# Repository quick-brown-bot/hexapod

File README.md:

# Hexapod

An ESP32-powered hexapod robot built as a long-term robotics and embedded systems project.

The goal is not just to make a robot walk, but to learn and at the same time build a platform that is easy to experiment with, tune, and extend. Most robot behavior is configurable at runtime, control inputs are transport-independent, and the motion stack is organized into separated components.

The project combines firmware, hardware design, and system documentation in a single repository.

> 6 legs, 18 servos, ESP32, ESP-IDF, FreeRTOS, direct PWM.

The distributed RS485/RP2040 leg-controller generation of this project has moved to a separate repository: [quick-brown-bot/hexapod_v2](https://github.com/quick-brown-bot/hexapod_v2). This repo covers the original ESP32 direct-PWM robot only. V1 is closed: the hardware and firmware here are done and kept for reference and continued use, not further development.

---

## What Is In This Repository

The repository contains software and hardware assets used to develop and validate the robot.

```text
firmware/
└── mainboard/         Main robot firmware (ESP32, direct PWM)

hardware/
├── servo_mainboard/   Central ESP32 board driving the servos directly
├── leg/               Leg controller board
├── esp32_connector/   ESP32 carrier / breakout
├── symbols/           Symbol libraries
├── footprints/        Footprint libraries
└── models/            Mechanical models

docs/
├── common/            Docs shared across subsystems (RPC, WiFi, config)
├── architecture/       System and hardware architecture docs
├── development/        Development docs
└── plans/             Project-wide backlog and research items
```

Mainboard firmware overview: [firmware/mainboard/README.md](firmware/mainboard/README.md)

The main firmware is built around a fixed 100 Hz control loop and a modular motion pipeline:

```text
Controller Input
        ↓
Gait Scheduler
        ↓
Foot Trajectory Generation
        ↓
Inverse Kinematics
        ↓
Motion Limiting
        ↓
Servo Outputs
```

---

## Current Technical Highlights

## Effort Summary

| Effort Area | Scope | Current Status | Notes |
| --- | --- | --- | --- |
| Locomotion Pipeline | Command mapping, gait scheduler, swing trajectory, whole-body IK | Implemented | Runs in a fixed 100 Hz control loop |
| KPP Motion Limits | Velocity, acceleration, jerk limiting and state estimation | Implemented | Runtime limits are configuration-backed |
| Controller Abstraction | Driver-agnostic core plus transport-specific drivers | Implemented | FlySky iBUS, Wi-Fi TCP, and Bluetooth Classic paths are present |
| RPC System | Queue-based command processing and config control | Implemented | Live inspection and runtime tuning are available |
| Configuration Platform | Namespace defaults, migration, discovery, persistence | Implemented | Core runtime namespaces are already consumed by modules |
| Configurator Tooling | External tuning and visualization UX | Planned | Firmware-side groundwork exists; UI work remains |

## Hardware Snapshot

- MCU: ESP32 running FreeRTOS through ESP-IDF.
- Robot layout: 6 legs, 3 degrees of freedom per leg, 18 hobby servos total.
- Power: 4S LiPo, separate UBEC paths for servo and logic power.
- PWM: mixed MCPWM and LEDC to reach all 18 outputs on the ESP32.
- Mechanical: custom 3D-printed chassis and leg parts.

## High-Level Architecture

```mermaid
flowchart LR
        Control[Controller stack]
        Config[RPC and config]
        App[Application loop]
        Loc[Locomotion]
        Limits[Motion limiting]
        Act[Actuation]
        Robot[Robot hardware]

        Control --> App
        Config --> App
        App --> Loc --> Limits --> Act --> Robot
        Config --> Control
```

- Controller stack: receives operator input from supported transports and normalizes it.
- RPC and config: handles runtime commands, parameter discovery, persistence, and save flows.
- Application loop: owns boot order and the 100 Hz control cycle.
- Locomotion: turns operator intent into gait phase, foot targets, and joint-space commands.
- Motion limiting: constrains commanded motion to configured dynamic envelopes.
- Actuation: maps joint commands to the PWM outputs that drive the robot.

### Runtime Configuration

Configuration is treated as a first-class subsystem rather than a collection of compile-time constants.

Parameters are organized into namespaces. Each namespace owns:

- parameter definitions,
- default values,
- validation rules,
- persistence behavior,
- migration logic,
- RPC discovery metadata.

The configuration manager provides:

- runtime parameter inspection,
- runtime modification,
- save/load operations,
- namespace registration,
- NVS persistence,
- version-aware migration support.

Robot geometry, calibration data, controller settings, motion limits, and other runtime behavior are loaded through this system rather than being hardcoded throughout the codebase.

### Motion Pipeline

The locomotion stack converts user commands into joint targets through a sequence of dedicated subsystems:

- gait scheduling,
- swing trajectory generation,
- inverse kinematics,
- velocity limiting,
- acceleration limiting,
- jerk limiting,
- servo actuation.

The motion loop runs at 100 Hz.

### Controller Abstraction

Controller transports are separated from locomotion.

Supported ingress paths currently include:

- FlySky iBUS,
- Wi-Fi TCP,
- Bluetooth Classic.

Each transport driver translates incoming data into a normalized controller state consumed by the motion system.

This allows locomotion, gait generation, and motion limiting to remain independent of transport-specific protocols.

### Hardware-Aware Design

The robot uses 18 servos arranged as three joints per leg:

- Coxa
- Femur
- Tibia

Servo signal generation is implemented on ESP32 using a combination of MCPWM and LEDC peripherals to fit within available hardware resources.

Power for logic and servos is separated to improve stability under heavy load.

---

## Engineering Problems Being Explored

This project is primarily a learning and engineering platform.

Current focus areas include:

- real-time control on resource-constrained hardware,
- gait generation and scheduling,
- inverse kinematics,
- motion smoothing and trajectory constraints,
- configuration architecture for embedded systems,
- transport-independent control interfaces,
- robotics software maintainability,
- practical servo-driven locomotion.

---

## Documentation

The repository contains detailed documentation covering implementation details and architecture decisions.

- [docs/architecture/SYSTEM_ARCHITECTURE.md](docs/architecture/SYSTEM_ARCHITECTURE.md)
- [docs/architecture/HARDWARE_AND_MECHANICS.md](docs/architecture/HARDWARE_AND_MECHANICS.md)
- [firmware/mainboard/README.md](firmware/mainboard/README.md)

**Common:**
- [docs/common/interfaces/RPC_USER_GUIDE.md](docs/common/interfaces/RPC_USER_GUIDE.md)
- [docs/common/configuration/CONFIGURATION_PERSISTENCE_DESIGN.md](docs/common/configuration/CONFIGURATION_PERSISTENCE_DESIGN.md)

Full documentation index: [docs/README.md](docs/README.md)

---

## Project Status

The project is under active development.

Current work focuses on improving locomotion quality, refining control architecture boundaries, and preparing the next generation of leg electronics while keeping the existing robot operational as a test platform.

---

## License

This repository uses Apache License 2.0 for the mainboard firmware.

License file location: [LICENSE](LICENSE)

Include the following notice in derivative works:

```text
Copyright 2025 Pawel Grudzien

Licensed under the Apache License, Version 2.0 (the "License");
you may not use this file except in compliance with the License.
You may obtain a copy of the License at

    http://www.apache.org/licenses/LICENSE-2.0

Unless required by applicable law or agreed to in writing, software
distributed under the License is distributed on an "AS IS" BASIS,
WITHOUT WARRANTIES OR CONDITIONS OF ANY KIND, either express or implied.
See the License for the specific language governing permissions and
limitations under the License.
```

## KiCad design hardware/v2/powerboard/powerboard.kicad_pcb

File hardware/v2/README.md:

# Hexapod V2 boards

Schematics for the [V2 system architecture](../../docs/architecture/HEXAPOD_V2_SYSTEM_ARCHITECTURE.md):
distributed leg controllers with logic power separated from servo power. V1
(`hardware/servo_mainboard`, `hardware/leg`, `hardware/esp32_connector`) is left
untouched — V2 lives here in parallel.

Three boards:

| Board | Source | Role |
|-------|--------|------|
| [MainBoard](mainboard/) | [`mainboard_sch.py`](mainboard/mainboard_sch.py) | ESP32 + IMU + RS485 master + 6× RJ11. Logic & comms only. |
| [LegBoard](legboard/) | [`legboard_sch.py`](legboard/legboard_sch.py) | XIAO RP2040 + SP3485 + 3 servos + sensing. One per leg. |
| [MainPowerBoard](powerboard/) | [`powerboard_sch.py`](powerboard/powerboard_sch.py) | Battery → fuse/switch/protection → 3 UBECs + SBEC → legs. |

These schematics are authored **as code** with the
[`hardware-schematics`](../schematic/README.md) toolchain. The Python script is
the source of truth; `uuids.json` is the committed UUID registry that protects
the PCB layout across regenerations. Edit the `.py`, never the `.kicad_sch` by
hand.

## Regenerating

```bash
python hardware/v2/mainboard/mainboard_sch.py
python hardware/v2/legboard/legboard_sch.py
python hardware/v2/powerboard/powerboard_sch.py
```

Each writes its `<board>.kicad_sch` and updates `<board>/uuids.json` (additions
only for unchanged parts). `hardware/v2/_common.py` resolves symbol libraries:
stock KiCad libs from the install (override with `KICAD_SYMBOL_DIR`), plus the
v2-local libraries under [`symbols/`](symbols/) — the Seeed XIAO series
(`Seeed_Studio_XIAO_Series.kicad_sym`), the ESP32 module (`SymbolsLib.kicad_sym`),
and `Hexapod_V2.kicad_sym` (flattened standalone `RJ25` and `SP3485CN`, because
the stock library defines those as derived `(extends …)` symbols the code
importer cannot follow).

V2 is self-contained: its own copy of the symbol libraries, footprints, and the
v2 FreeCAD model live here under [`symbols/`](symbols/), [`footprints/`](footprints/)
and [`models/`](models/); the boards do not depend on shared top-level libraries.

## Inter-board connections

```text
MainPowerBoard.J_LOGIC (+5V) ──► MainBoard.J7 (SBEC_5V_IN)
MainBoard.J1..J6 (RJ11)      ──► LegBoard.J1 (UPLINK_RJ11)        ×6
MainPowerBoard.J1..J6 (+6V)  ──► LegBoard.J5 (SERVO_PWR_IN)       ×6
```

### RJ11 / RJ25 leg link (MainBoard ↔ LegBoard)

The physical cable is populated as a 4-wire link inside a 6P6C/RJ25 shell, so
pins 1 and 6 are intentionally left unconnected.

| Pin | Net | Function |
|-----|-----|----------|
| 1 | — | unused |
| 2 | GND | Ground |
| 3 | RS485_A | RS485 A |
| 4 | RS485_B | RS485 B |
| 5 | +5V | Logic power |
| 6 | — | unused |

## MainBoard nets

| Net | Connects |
|-----|----------|
| `+5V` | SBEC input (J7), ESP32 dev-board VIN, all six RJ11 pin 5 |
| `+3.3V` | ESP32 dev-board 3V3 output, SP3485 VCC, IMU, decoupling, EN pull-up |
| `GND` | global ground |
| `ESP_TXD` / `ESP_RXD` | ESP32 IO17/IO16 (UART2) ↔ SP3485 DI/RO |
| `RS485_DE` | ESP32 IO4 → SP3485 DE + ~RE (direction) |
| `RS485_A` / `RS485_B` | SP3485 A/B ↔ all six RJ11, 120 Ω term (R1) |
| `IMU_SDA` / `IMU_SCL` / `IMU_INT` | ESP32 IO21/IO22/IO34 ↔ IMU header (J9) |

MainBoard decoupling intent (implemented in schematic code): `C1` 10 uF on +5V at
power entry (close to J7/U1 VIN), `C2` 100 nF at ESP32 3V3 pins, `C3` 100 nF at
SP3485 VCC, `C4` 100 nF at IMU header power pins, and `C5` 10 uF bulk on +3.3V
near the ESP32 3V3-source/load hub.

IMU header J9 (`Conn_01x05`): 1 = +3.3V, 2 = GND, 3 = SDA, 4 = SCL, 5 = INT.

Footprints currently driven from the generator: `U1` uses
`Custom:ESP32_Dev_Board`, `J1..J6` use
`Connector_RJ:RJ25_Wayconn_MJEA-660X1_Horizontal`, `J9` uses
`Connector_PinHeader_2.54mm:PinHeader_1x05_P2.54mm_Vertical`, `U2` uses the
SOIC-8 SP3485 footprint, and the ordinary small R/C parts default to 0805.

## LegBoard nets

| Net | Connects |
|-----|----------|
| `+5V` | RJ11 pin 5 logic power → XIAO VBUS (U1.14) |
| `+3.3V` | XIAO 3V3 out (U1.12) → SP3485 VCC, INA4181 VCC, decoupling |
| `+6V` | post-total-shunt servo bus; high-side **force** node feeding the three per-servo branch shunts and bulk cap C2 |
| `+6V_IN` | raw servo-power input (J5) ahead of the total shunt |
| `+6V_COXA` / `+6V_FEMUR` / `+6V_TIBIA` | post-branch-shunt servo supply rails (force) for J2 / J3 / J4 |
| `ITOT_SP` / `ITOT_SN` | Kelvin **sense** taps of total shunt R4 → INA IN+1 / IN-1 |
| `COXA_SP` / `COXA_SN` | Kelvin sense taps of coxa shunt R5 → INA IN+4 / IN-4 |
| `FEMUR_SP` / `FEMUR_SN` | Kelvin sense taps of femur shunt R3 → INA IN+2 / IN-2 |
| `TIBIA_SP` / `TIBIA_SN` | Kelvin sense taps of tibia shunt R2 → INA IN+3 / IN-3 |
| `GND` | global ground |
| `RP_TXD` / `RP_RXD` | XIAO P0/P1 (UART) ↔ SP3485 DI/RO |
| `RS485_DE` | XIAO P6/D4 → SP3485 DE + ~RE |
| `RS485_A` / `RS485_B` | SP3485 ↔ RJ11, 120 Ω term R1 (DNP except bus ends) |
| `COXA_PWM` / `FEMUR_PWM` / `TIBIA_PWM` | XIAO P3/P4/P2 → servo connectors J2/J3/J4 |
| `I_TOTAL_SENSE` | INA4181 channel 1 output → XIAO A0 |
| `I_FEMUR_SENSE` | INA4181 channel 2 output → XIAO A1 |
| `I_TIBIA_SENSE` | INA4181 channel 3 output → XIAO A2 |
| `I_COXA_SENSE` | INA4181 channel 4 output → XIAO A3 |

Servo connectors J2/J3/J4 (`Conn_01x03`): 1 = signal, 2 = branch +6V, 3 = GND.
J5 is a 2-pin screw terminal for servo power input. The four current shunts
`R2`/`R3`/`R4`/`R5` are **4-terminal (Kelvin) shunts** (`Device:R_Shunt`): pins
1/4 carry current, pins 2/3 are the sense taps. Each INA input reaches the shunt
over its own unique two-node `*_SP`/`*_SN` net, so the autorouter cannot merge
the three high-side taps (INA pins 6/15/17) through the shared `+6V` copper or
assign them current-rail trace widths. U3 (`INA4181A3IPWR`, gain 100) measures channel 1 across the total-leg shunt
`R4` (`+6V_IN`→`+6V`), channel 2 across femur `R3`, channel 3 across tibia
`R2`, channel 4 across coxa `R5`; IN+ is always on the higher-potential
(source) side. The generated sheet layout keeps the XIAO and INA
blocks as top-level anchors with the connector and power groups below for
readability.

> **Shunt placement must stay at rotation 0.** The schematic-as-code pin
> transform mismatches KiCad for off-axis pins at rotation 90/270 — the Kelvin
> sense pads land off the pin and the force pads swap. Verified via netlist
> export; keep the `Device:R_Shunt` placements un-rotated.

Footprints currently driven from the generator: `U1` uses
`Seeed_Studio_XIAO_Series:XIAO-RP2040-DIP`, `J1` uses
`Connector_RJ:RJ25_Wayconn_MJEA-660X1_Horizontal`, `U2` uses the SOIC-8
SP3485 footprint, `U3` uses `Custom:PW20_TEX`, `J2`/`J3`/`J4` use
`Connector_PinHeader_2.54mm:PinHeader_1x03_P2.54mm_Vertical`, `J5` uses
`TerminalBlock:TerminalBlock_MaiXu_MX126-5.0-02P_1x02_P5.00mm`, the four INA
shunts now use the 4-contact Kelvin footprint
`Resistor_SMD:R_Shunt_Ohmite_LVK12`, `C2` uses the through-hole radial candidate
`Capacitor_THT:CP_Radial_D8.0mm_P3.50mm` for an 8 mm diameter bulk capacitor, and
the ordinary small R/C parts default to 0805. Verify the LVK12 shunt power rating
and the capacitor lead pitch / body height against the exact parts before
freezing the PCB.

## MainPowerBoard nets

| Net | Connects |
|-----|----------|
| `BATT_RAW`→`BATT_FUSED`→`+VMAIN` | battery → F1 fuse → Q1/Q2 parallel PMOS reverse-polarity stage → main rail |
| `+VMAIN` | feeds the three UBEC modules (J8/J9/J10), the SBEC (J11), monitor (J13), bulk C4 |
| `VSERVO1` | UBEC1 out → legs 1,2 (J1,J2), bulk C1, LED D2 |
| `VSERVO2` | UBEC2 out → legs 3,4 (J3,J4), bulk C2, LED D3 |
| `VSERVO3` | UBEC3 out → legs 5,6 (J5,J6), bulk C3, LED D4 |
| `+5V` | SBEC out (J11) → logic output (J12), LED D5 |
| `GND` | global ground |

UBEC/SBEC module headers (`Conn_01x04`): 1 = +VMAIN in, 2 = GND, 3 = regulated
out, 4 = GND. Monitor header J13 (`Conn_01x05`): +VMAIN, VSERVO1, VSERVO2,
VSERVO3, GND.

`F1` is a soldered-in (non-replaceable) SMD fuse, Schurter 3413.0331.22
(20A, time-lag, 1206/`Fuse:Fuse_1206_3216Metric`) — chosen over an automotive
mini-blade holder because TME stocks no SMD blade-fuse holder; the previous
`Custom:Fuse Holder Mini` THT holder footprint is unused now but left in the
library.

Footprints currently driven from the generator: `J7` (battery input) uses
`Connector_Wire:SolderWire-1.5sqmm_1x02_P7.8mm_D1.7mm_OD3.9mm` solder pads,
`J1..J6` use
`TerminalBlock:TerminalBlock_MaiXu_MX126-5.0-02P_1x02_P5.00mm`, and `J13` uses
`Connector_PinHeader_2.54mm:PinHeader_1x05_P2.54mm_Vertical`. Bulk caps use
`C1..C3`: `Capacitor_THT:CP_Radial_D13.0mm_P5.00mm` (2200 uF class) and `C4`:
`Capacitor_THT:CP_Radial_D8.0mm_P3.80mm` (1000 uF class). The status resistor /
LED parts default to 0805. Reverse-polarity protection uses two parallel
`FQP47P06` PMOS parts in `Package_TO_SOT_THT:TO-220-3_Vertical`.

Power-entry control is now low-current at SW1: the high-current path is
`BATT_FUSED -> Q1/Q2 -> +VMAIN`, while SW1 only drives the PMOS gates through
`R7=10k` + `Q3` (NPN pull-down), with `R6=100k` pull-up and `R5=100R` series
gate resistor for damping.

Pre-prototype hardening now added in-code:
- `R8=100k` from `NPN_BASE` to `GND` (base pull-down; avoids floating base when SW1 is open).
- `D6=15V` Zener between `PMOS_GATE` and `BATT_FUSED` (Vgs transient clamp).
- Optional `C5=100nF` from `PMOS_GATE_DRV` to `GND` (slows turn-on edge to soften inrush into ~7600 uF total bulk capacitance).

## PCB order tagging

Each board order placed with JLCPCB is tagged in git at the exact commit that
was sent to manufacture:

```
git tag pcb_order_<JLCPCB-order-ID> <commit>
```

Example: `pcb_order_W2026062121528170` points to the first legboard/mainboard
order. To inspect or check out any ordered revision:

```bash
git show pcb_order_W2026062121528170          # view commit
git checkout pcb_order_W2026062121528170      # restore that state
```

This makes it possible to diff the current schematic against what was actually
fabricated, or to flash firmware that matches the physical board on hand.

---

## Status / known limitations (first pass)

These are deliberate module-abstraction simplifications to refine in Eeschema
before fabrication:

* **Reverse-polarity protection** now uses two parallel PMOS parts (`Q1`/`Q2`,
  `FQP47P06`) to leave thermal headroom for high current, plus a low-current
  gate-driver stage (`Q3`, `R5`, `R6`, `R7`, `R8`) so SW1 does not switch inrush
  current directly.
* **UBEC / SBEC / IMU / current sensor** are represented as module headers, not
  discrete designs.
* **ERC** loads cleanly but reports expected violations: unused ESP32/XIAO GPIO
  and the ESP32 `VIN`/`SENSOR_*` pins are left open (add no-connect flags), and
  off-grid endpoints (the loose auto-layout is meant to be re-placed in
  Eeschema). Net-label connectivity is verified correct via exported netlist.
* **Remaining footprint work** is limited to the high-current / bulk power-path
  parts and the placeholder module headers; the ordinary V2 passives, ESP32,
  XIAO RP2040, RJ25 connectors, and the IMU header are now assigned in code.

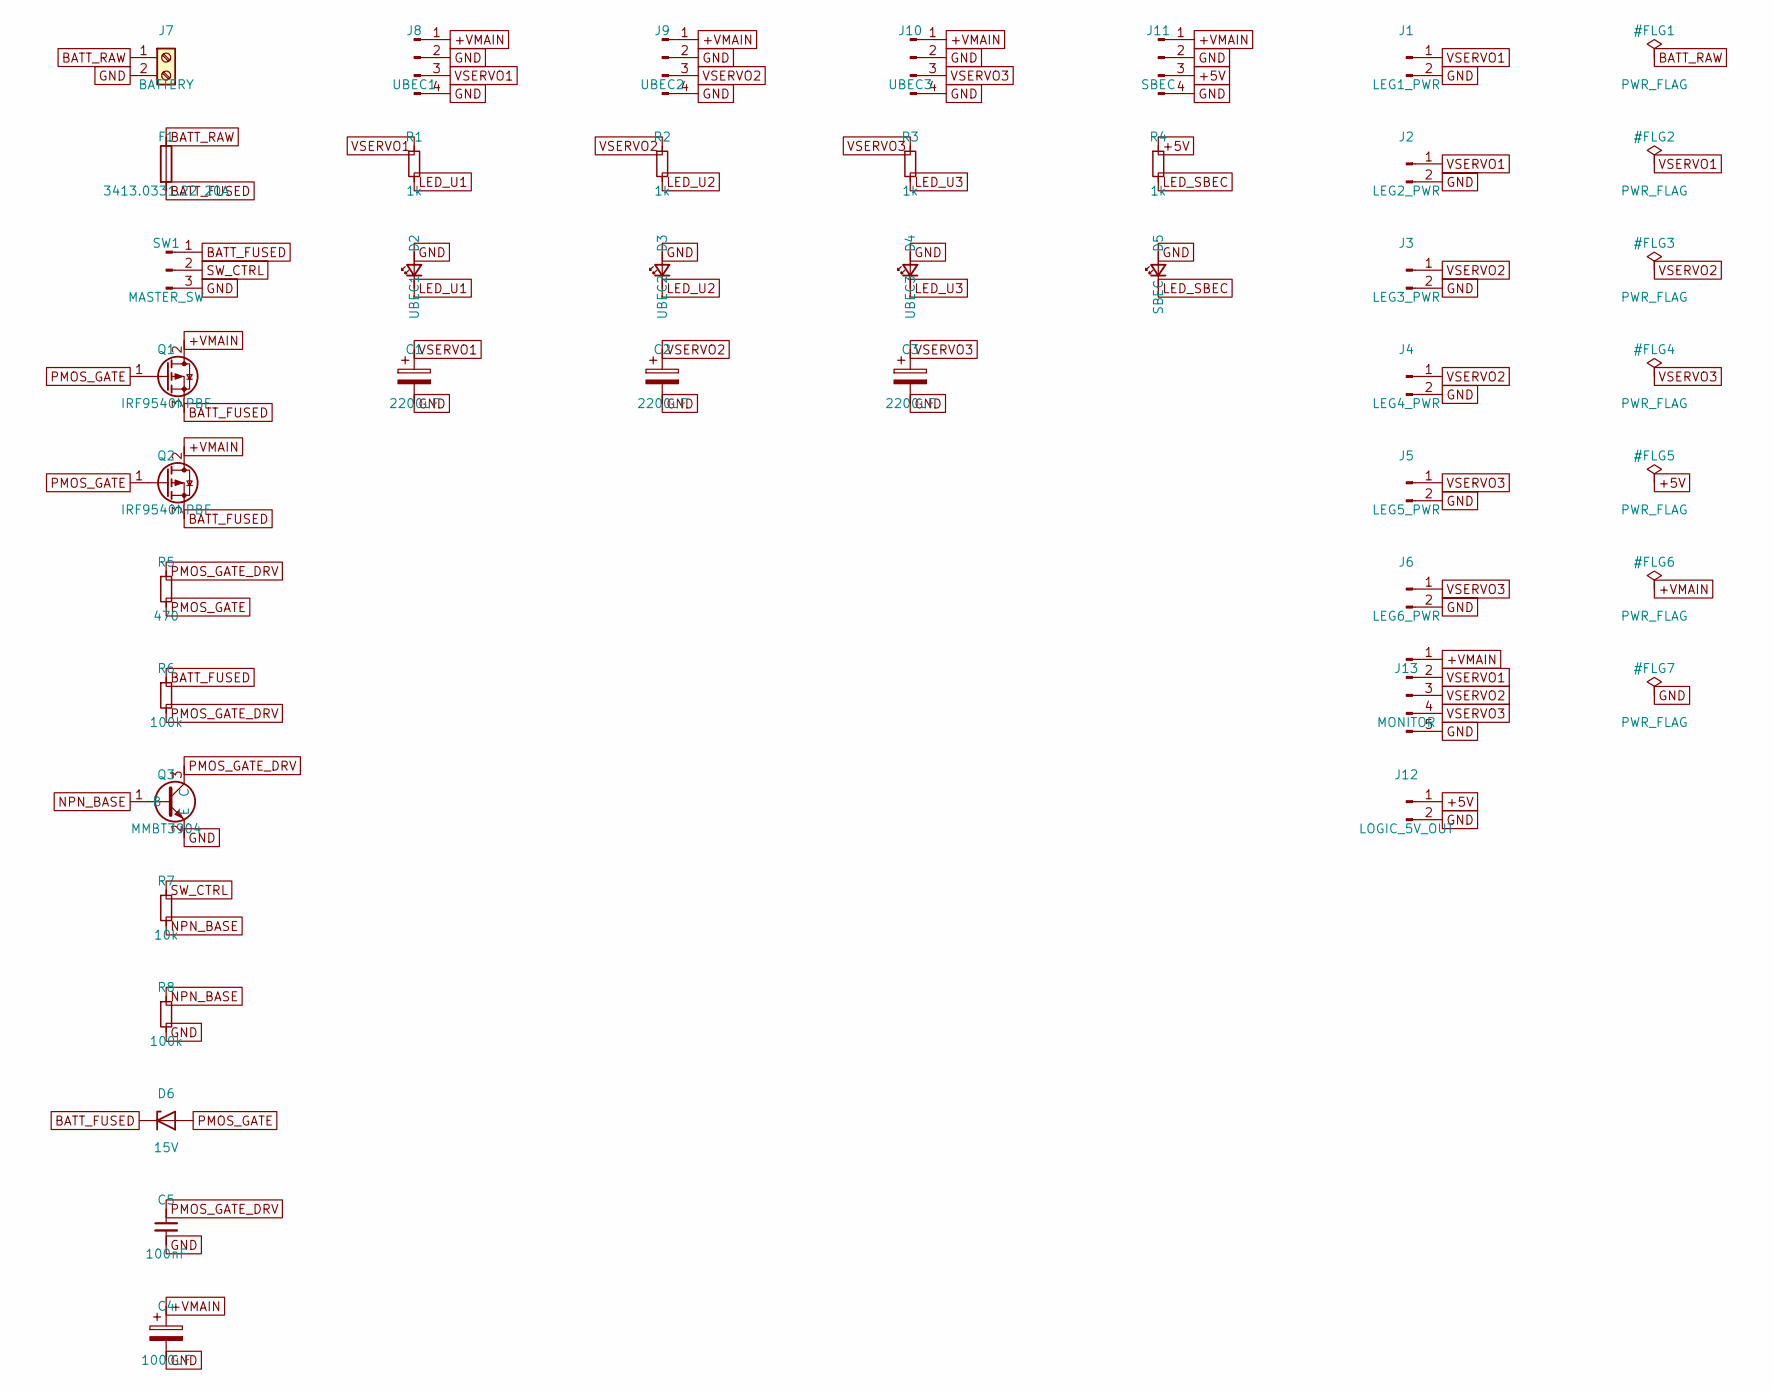
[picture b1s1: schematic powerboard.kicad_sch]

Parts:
C1, C2, C3: 2200uF; CP_Radial_D13.0mm_P5.00mm
C4: 1000uF; CP_Radial_D8.0mm_P3.80mm
C5: 100nF; C_0805_2012Metric
D2: UBEC1; LED_0805_2012Metric
D3: UBEC2; LED_0805_2012Metric
D4: UBEC3; LED_0805_2012Metric
D5: SBEC; LED_0805_2012Metric
D6: 15V; D_0805_2012Metric
F1: 3413.0331.22 20A; Fuse_1206_3216Metric
J1: LEG1_PWR; TerminalBlock_MaiXu_MX126-5.0-02P_1x02_P5.00mm
J2: LEG2_PWR; TerminalBlock_MaiXu_MX126-5.0-02P_1x02_P5.00mm
J3: LEG3_PWR; TerminalBlock_MaiXu_MX126-5.0-02P_1x02_P5.00mm
J4: LEG4_PWR; TerminalBlock_MaiXu_MX126-5.0-02P_1x02_P5.00mm
J5: LEG5_PWR; TerminalBlock_MaiXu_MX126-5.0-02P_1x02_P5.00mm
J6: LEG6_PWR; TerminalBlock_MaiXu_MX126-5.0-02P_1x02_P5.00mm
J7: BATTERY; SolderWire-1.5sqmm_1x02_P7.8mm_D1.7mm_OD3.9mm
J8: UBEC1; SolderWire-0.25sqmm_1x04_P4.2mm_D0.65mm_OD1.7mm
J9: UBEC2; SolderWire-0.25sqmm_1x04_P4.2mm_D0.65mm_OD1.7mm
J10: UBEC3; SolderWire-0.25sqmm_1x04_P4.2mm_D0.65mm_OD1.7mm
J11: SBEC; SolderWire-0.25sqmm_1x04_P4.2mm_D0.65mm_OD1.7mm
J12: LOGIC_5V_OUT; PinHeader_1x02_P2.54mm_Vertical
J13: MONITOR; PinHeader_1x05_P2.54mm_Vertical
Q1, Q2: IRF9540NPBF; TO-220-3_Vertical
Q3: MMBT3904; SOT-23
R1, R2, R3, R4: 1k; R_0805_2012Metric
R5: 470; R_0805_2012Metric
R6, R8: 100k; R_0805_2012Metric
R7: 10k; R_0805_2012Metric
SW1: MASTER_SW; SW_Slide_SPDT_Straight

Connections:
+5V: J11.3, J12.1, R4.1
+VMAIN: C4.1, J8.1, J9.1, J10.1, J11.1, J13.1, Q1.2 (D), Q2.2 (D)
BATT_FUSED: D6.1 (K), F1.2, Q1.3 (S), Q2.3 (S), R6.1, SW1.1
BATT_RAW: F1.1, J7.1
GND: C1.2, C2.2, C3.2, C4.2, C5.2, D2.2 (A), D3.2 (A), D4.2 (A), D5.2 (A), J1.2, J2.2, J3.2, J4.2, J5.2, J6.2, J7.2, J8.2, J8.4, J9.2, J9.4, J10.2, J10.4, J11.2, J11.4, J12.2, J13.5, Q3.2 (E), R8.2, SW1.3
LED_SBEC: D5.1 (K), R4.2
LED_U1: D2.1 (K), R1.2
LED_U2: D3.1 (K), R2.2
LED_U3: D4.1 (K), R3.2
NPN_BASE: Q3.1 (B), R7.2, R8.1
PMOS_GATE: D6.2 (A), Q1.1 (G), Q2.1 (G), R5.2
PMOS_GATE_DRV: C5.1, Q3.3 (C), R5.1, R6.2
SW_CTRL: R7.1, SW1.2
VSERVO1: C1.1, J1.1, J2.1, J8.3, J13.2, R1.1
VSERVO2: C2.1, J3.1, J4.1, J9.3, J13.3, R2.1
VSERVO3: C3.1, J5.1, J6.1, J10.3, J13.4, R3.1

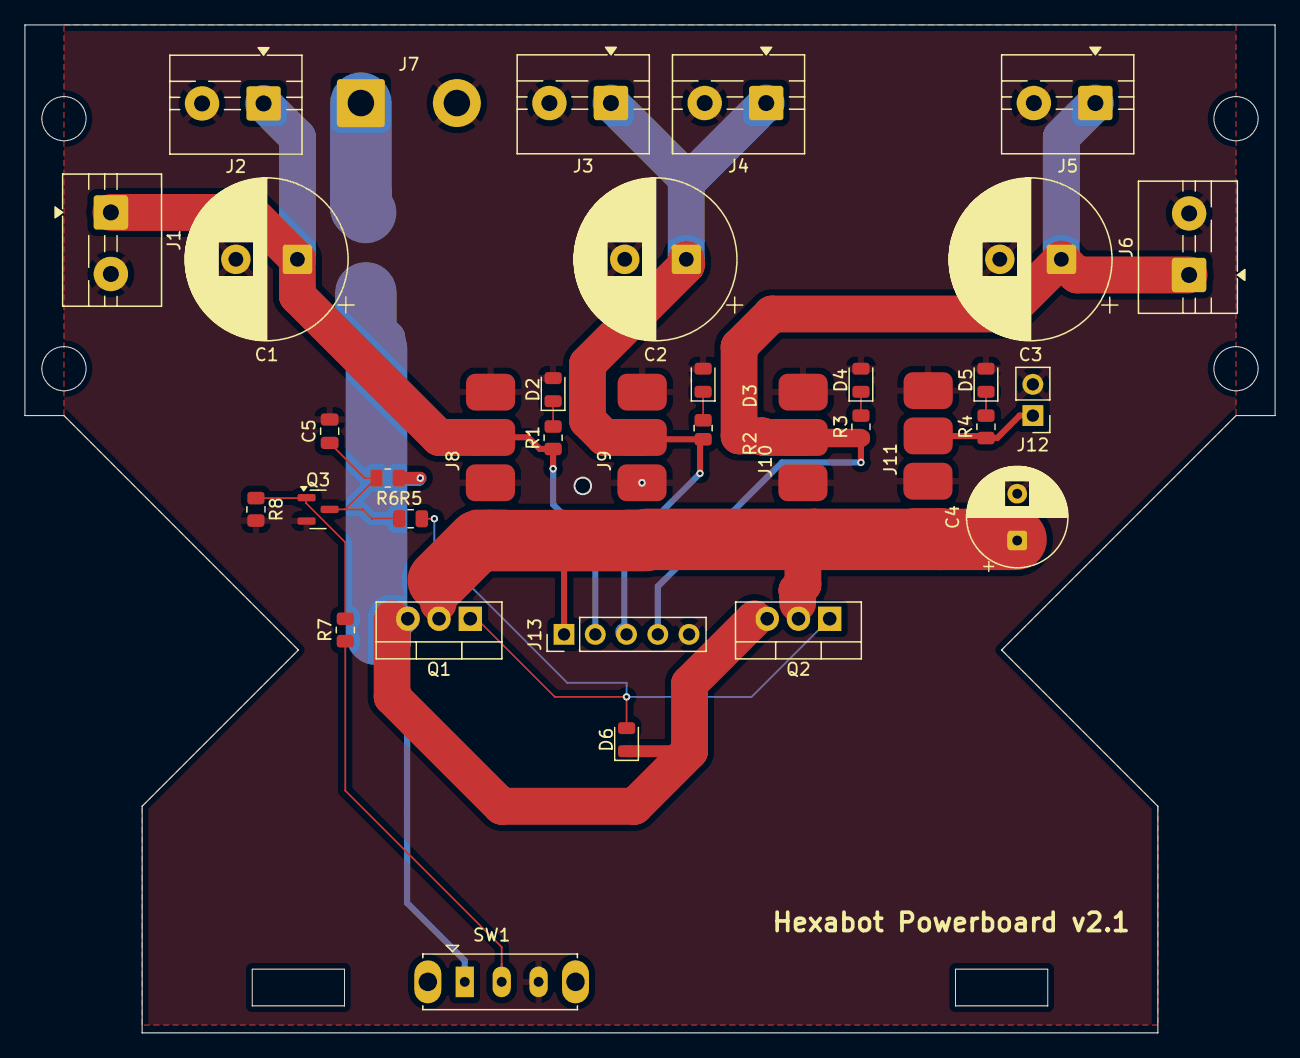
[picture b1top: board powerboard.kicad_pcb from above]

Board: 2 copper layers, 101.6 x 81.9 mm, 36 parts (1 on the bottom side), 16 nets.

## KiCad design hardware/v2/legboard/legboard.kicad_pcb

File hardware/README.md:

# Hexapod boards

The electrical design: a centralized controller that drives the servos directly.

This folder is self-contained — its own copy of the symbol libraries and
footprints lives alongside the designs, so the boards do not depend on any
shared top-level libraries.

| Board | Files | Role |
|-------|-------|------|
| [servo_mainboard](servo_mainboard/) | `hexapod.kicad_*` | Central ESP32 board driving the servos directly. |
| [leg](leg/) | `leg_v2.kicad_*` | XIAO RP2040 leg controller (early distributed-leg experiment). |
| [esp32_connector](esp32_connector/) | `esp32_connector.kicad_*` | ESP32 carrier / breakout. |

## Layout

```
hardware/
├── symbols/      ← Seeed XIAO + SymbolsLib (ESP32) symbol libraries
├── footprints/   ← Seeed XIAO footprints
├── models/       ← hexapod_v1.FCStd (mechanical model)
├── servo_mainboard/
├── leg/
└── esp32_connector/
```

The board project library tables (`sym-lib-table` / `fp-lib-table`) reference
these local copies via `${KIPRJMOD}`-relative paths. Stock KiCad symbols
(`Device:*`, `Connector:*`, `RF_Module:*`, `power:*`) resolve from the KiCad
install's global library table.

These schematics are KiCad-native and edited in Eeschema.

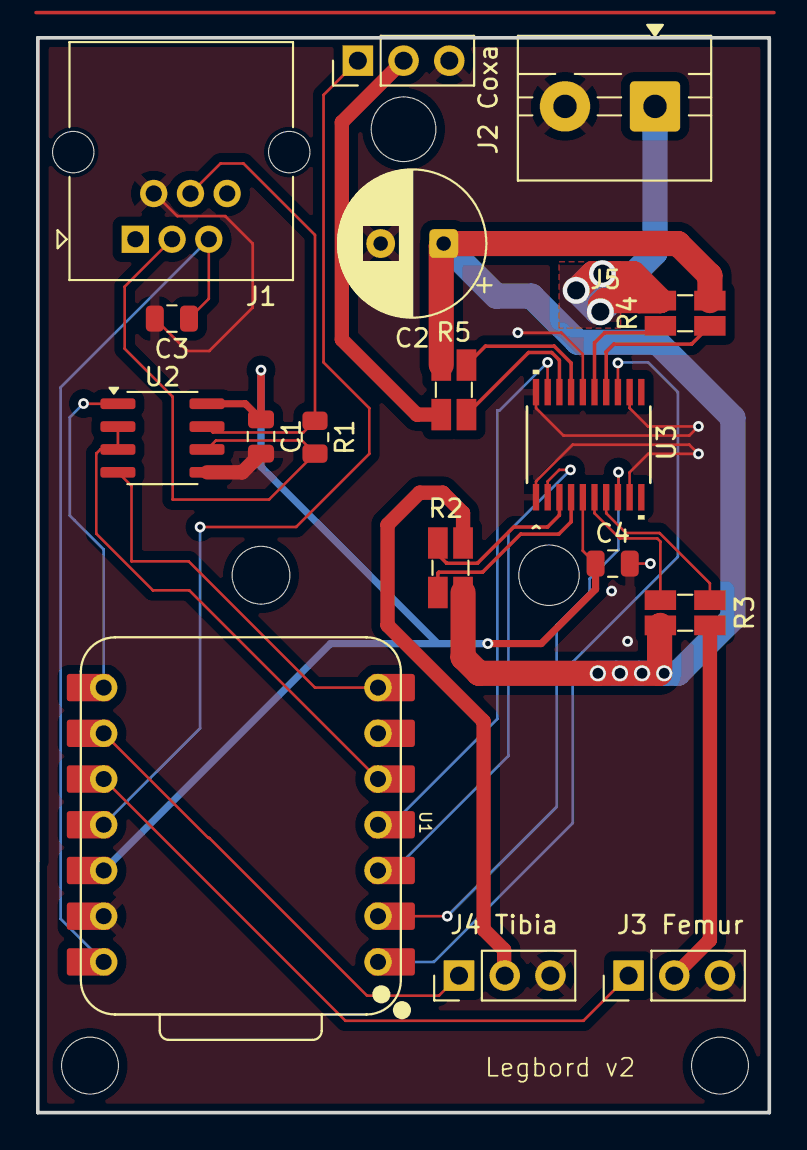
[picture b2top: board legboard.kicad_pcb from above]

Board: 2 copper layers, 40.6 x 59.7 mm, 17 parts (0 on the bottom side), 28 nets.

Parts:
C1, C3, C4: 100nF; C_0805_2012Metric
C2: 470uF; CP_Radial_D8.0mm_P3.50mm
J1: UPLINK_RJ11; RJ25_Wayconn_MJEA-660X1_Horizontal
J2 Coxa: COXA; PinHeader_1x03_P2.54mm_Vertical
J3 Femur: FEMUR; PinHeader_1x03_P2.54mm_Vertical
J4 Tibia: TIBIA; PinHeader_1x03_P2.54mm_Vertical
J5: SERVO_PWR_IN; TerminalBlock_MaiXu_MX126-5.0-02P_1x02_P5.00mm
R1: 120 (DNP); R_0805_2012Metric
R2, R3, R4, R5: 0.01; R_Shunt_Ohmite_LVK12
U1: XIAO-RP2040; XIAO-RP2040-DIP
U2: SP3485CN; SOIC-8_3.9x4.9mm_P1.27mm
U3: INA4181A3IPWR; PW20_TEX

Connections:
+3.3V: C1.1, C4.1, U1.12 (3V3), U2.8 (VCC), U3.5 (VS)
+5V: C3.1, J1.5, U1.14 (VBUS)
+6V: C2.1, R2.1, R3.1, R4.4, R5.1
+6V_COXA: J2 Coxa.2, R5.4
+6V_FEMUR: J3 Femur.2, R3.4
+6V_IN: J5.1, R4.1
+6V_TIBIA: J4 Tibia.2, R2.4
COXA_PWM: J2 Coxa.1, U1.11 (P3_D10_MOSI)
COXA_SN: R5.3, U3.18 (IN-4)
COXA_SP: R5.2, U3.17 (IN+4)
FEMUR_PWM: J3 Femur.1, U1.10 (P4_D9_MISO)
FEMUR_SN: R3.3, U3.7 (IN-2)
FEMUR_SP: R3.2, U3.6 (IN+2)
GND: C1.2, C2.2, C3.2, C4.2, J1.2, J2 Coxa.3, J3 Femur.3, J4 Tibia.3, J5.2, U1.13 (GND), U2.5 (GND), U3.1 (REF1), U3.9 (REF2), U3.12 (REF3), U3.16 (GND), U3.20 (REF4)
ITOT_SN: R4.3, U3.14 (IN-3)
ITOT_SP: R4.2, U3.15 (IN+3)
I_COXA_SENSE: U1.4 (P29_A3_D3), U3.19 (OUT4)
I_FEMUR_SENSE: U1.2 (P27_A1_D1), U3.8 (OUT2)
I_TIBIA_SENSE: U1.3 (P28_A2_D2), U3.2 (OUT1)
I_TOTAL_SENSE: U1.1 (P26_A0_D0), U3.13 (OUT3)
RP_RXD: U1.8 (P1_D7_RX), U2.1 (RO)
RP_TXD: U1.7 (P0_D6_TX), U2.4 (DI)
RS485_A: J1.3, R1.2, U2.6 (A)
RS485_B: J1.4, R1.1, U2.7 (B)
RS485_DE: U1.5 (P6_SDA_D4), U2.2 (~RE), U2.3 (DE)
TIBIA_PWM: J4 Tibia.1, U1.9 (P2_D8_SCK)
TIBIA_SN: R2.3, U3.3 (IN-1)
TIBIA_SP: R2.2, U3.4 (IN+1)

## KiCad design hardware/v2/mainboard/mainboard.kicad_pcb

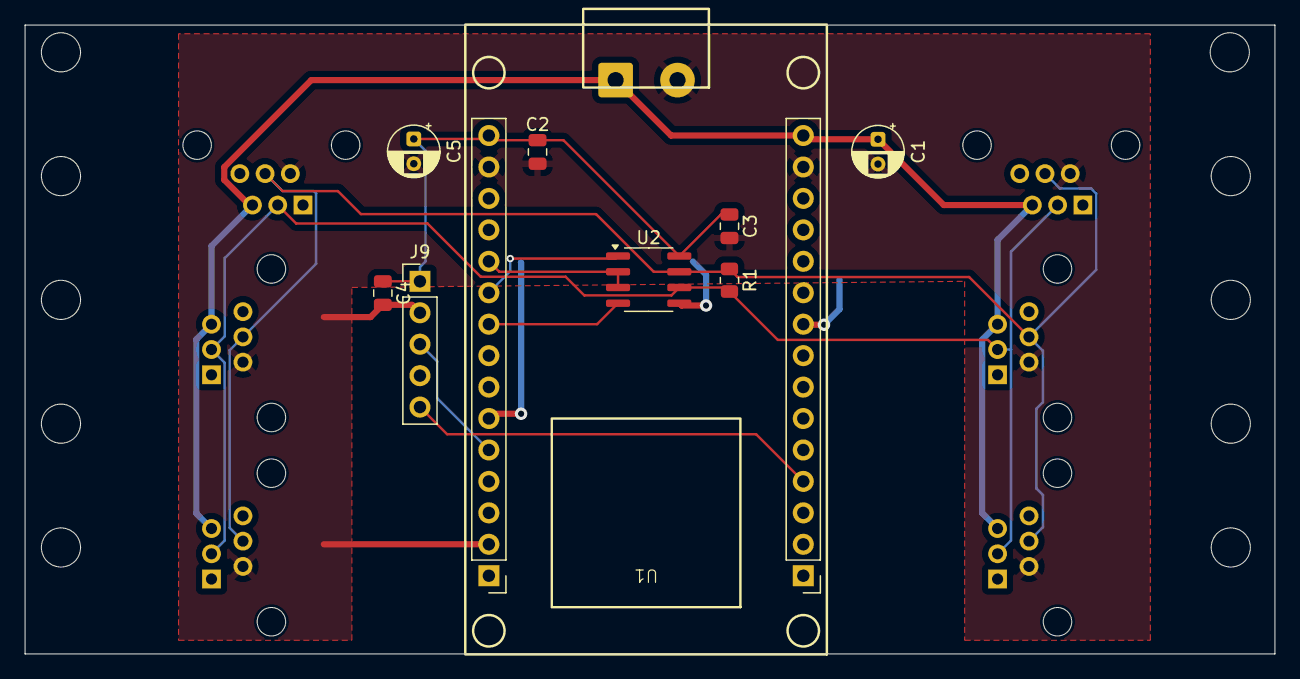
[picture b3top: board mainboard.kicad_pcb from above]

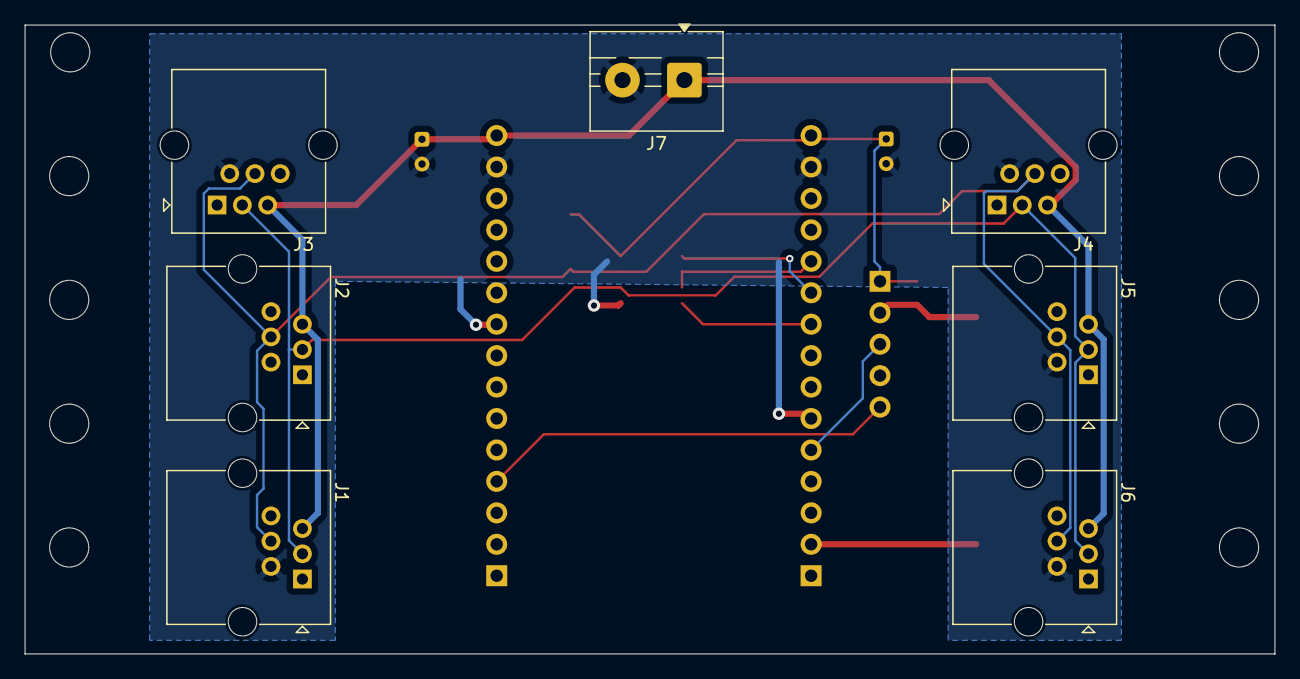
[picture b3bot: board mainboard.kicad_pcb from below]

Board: 2 copper layers, 101.0 x 50.8 mm, 16 parts (7 on the bottom side), 10 nets.

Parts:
C1, C5: 10uF; CP_Radial_D4.0mm_P2.00mm
C2, C3, C4: 100nF; C_0805_2012Metric
J1: LEG1_RJ11; RJ25_Wayconn_MJEA-660X1_Horizontal
J2: LEG2_RJ11; RJ25_Wayconn_MJEA-660X1_Horizontal
J3: LEG3_RJ11; RJ25_Wayconn_MJEA-660X1_Horizontal
J4: LEG4_RJ11; RJ25_Wayconn_MJEA-660X1_Horizontal
J5: LEG5_RJ11; RJ25_Wayconn_MJEA-660X1_Horizontal
J6: LEG6_RJ11; RJ25_Wayconn_MJEA-660X1_Horizontal
J7: SBEC_5V_IN; TerminalBlock_MaiXu_MX126-5.0-02P_1x02_P5.00mm
J9: IMU_I2C; PinHeader_1x05_P2.54mm_Vertical
R1: 120; R_0805_2012Metric
U1: ESP32-WROOM-32D; ESP32_Dev_Board
U2: SP3485CN; SOIC-8_3.9x4.9mm_P1.27mm

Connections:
+3.3V: C2.1, C3.1, C4.1, C5.1, J9.1, U1.3 (V3.3), U2.8 (VCC)
+5V: C1.1, J1.5, J2.5, J3.5, J4.5, J5.5, J6.5, J7.1, U1.2 (VIN)
ESP_RXD: U1.25 (IO16), U2.1 (RO)
ESP_TXD: U1.27 (IO17), U2.4 (DI)
GND: C1.2, C2.2, C3.2, C4.2, C5.2, J1.2, J2.2, J3.2, J4.2, J5.2, J6.2, J7.2, J9.2, U1.1 (GND), U1.15 (GND), U1.38 (GND), U1.39 (GND), U2.5 (GND)
IMU_INT: J9.5, U1.10 (IO34)
IMU_SDA: J9.3, U1.42 (IO21)
RS485_A: J1.3, J2.3, J3.3, J4.3, J5.3, J6.3, R1.2, U2.6 (A)
RS485_B: J1.4, J2.4, J3.4, J4.4, J5.4, J6.4, R1.1, U2.7 (B)
RS485_DE: U1.24 (IO4), U2.2 (~RE), U2.3 (DE)

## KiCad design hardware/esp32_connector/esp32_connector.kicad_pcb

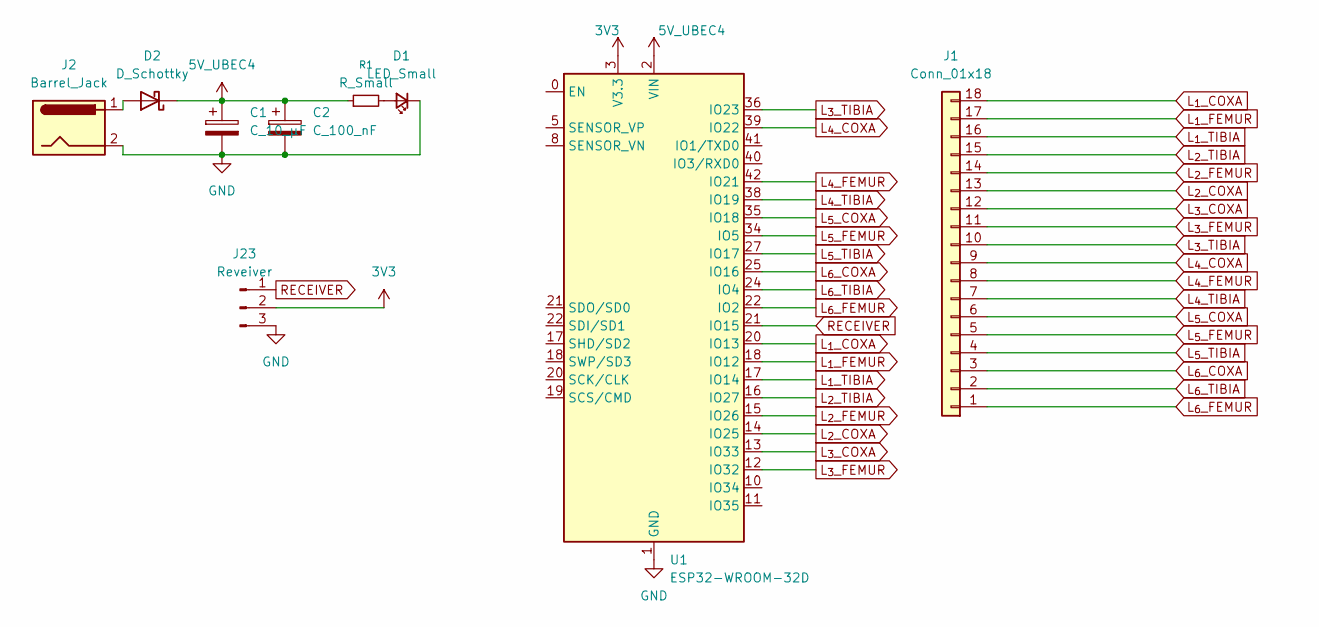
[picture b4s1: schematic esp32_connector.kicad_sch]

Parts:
C1: C_10_µF; C_1206_3216Metric
C2: C_100_nF; C_0805_2012Metric
D1: LED_Small; LED_0805_2012Metric
D2: D_Schottky; D_SOD-123
J1: Conn_01x18; TE_1-84952-8_1x18-1MP_P1.0mm_Horizontal
J2: Barrel_Jack; TerminalBlock_Phoenix_MKDS-1,5-2_1x02_P5.00mm_Horizontal
J23: Reveiver; PinHeader_1x03_P2.54mm_Vertical
R1: R_Small; R_0805_2012Metric
U1: ESP32-WROOM-32D; ESP32_Dev_Board

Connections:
3V3: J23.2, U1.3 (V3.3)
5V_UBEC4: C1.1, C2.1, D2.1 (K), R1.1, U1.2 (VIN)
L_{1}_COXA: J1.18, U1.20 (IO13)
L_{1}_FEMUR: J1.17, U1.18 (IO12)
L_{1}_TIBIA: J1.16, U1.17 (IO14)
L_{2}_COXA: J1.13, U1.14 (IO25)
L_{2}_TIBIA: J1.15, U1.16 (IO27)
L_{3}_COXA: J1.12, U1.13 (IO33)
L_{3}_FEMUR: J1.11, U1.12 (IO32)
L_{3}_TIBIA: J1.10, U1.36 (IO23)
L_{4}_FEMUR: J1.8, U1.42 (IO21)
L_{5}_COXA: J1.6, U1.35 (IO18)
L_{5}_FEMUR: J1.5, U1.34 (IO5)
L_{5}_TIBIA: J1.4, U1.27 (IO17)
L_{6}_COXA: J1.3, U1.25 (IO16)
L_{6}_FEMUR: J1.1, U1.22 (IO2)
L_{6}_TIBIA: J1.2, U1.24 (IO4)
unnamed: D1.2 (A), R1.2
unnamed: D2.2 (A), J2.1
RECEIVER: J23.1, U1.21 (IO15)

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
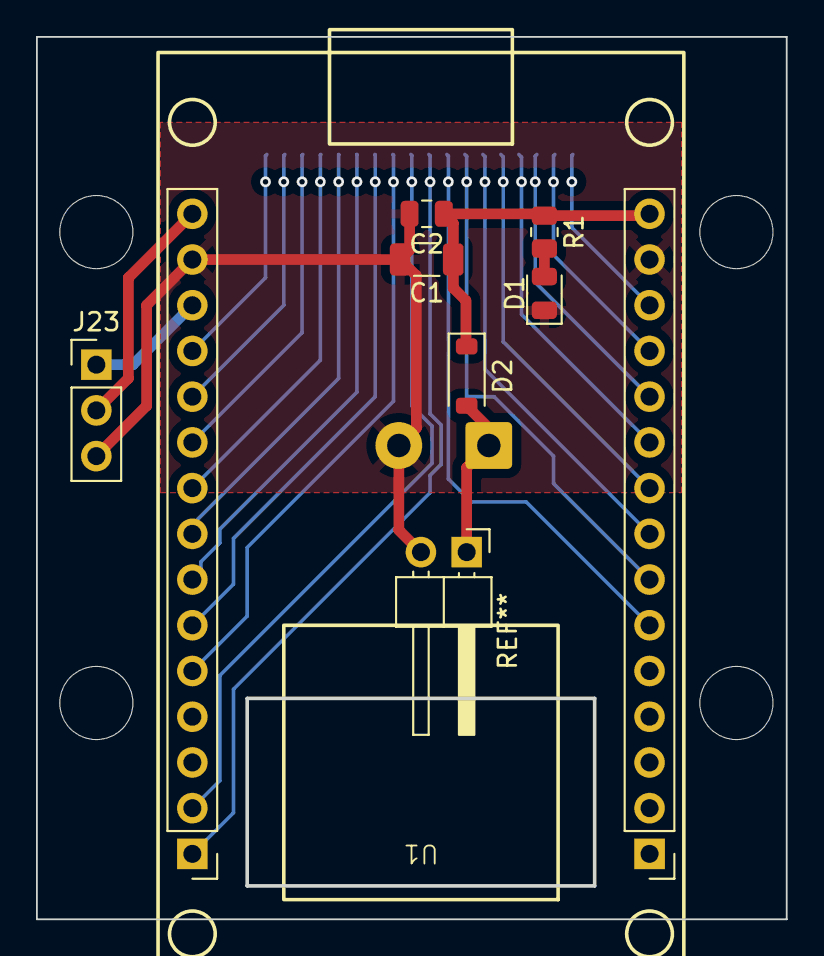
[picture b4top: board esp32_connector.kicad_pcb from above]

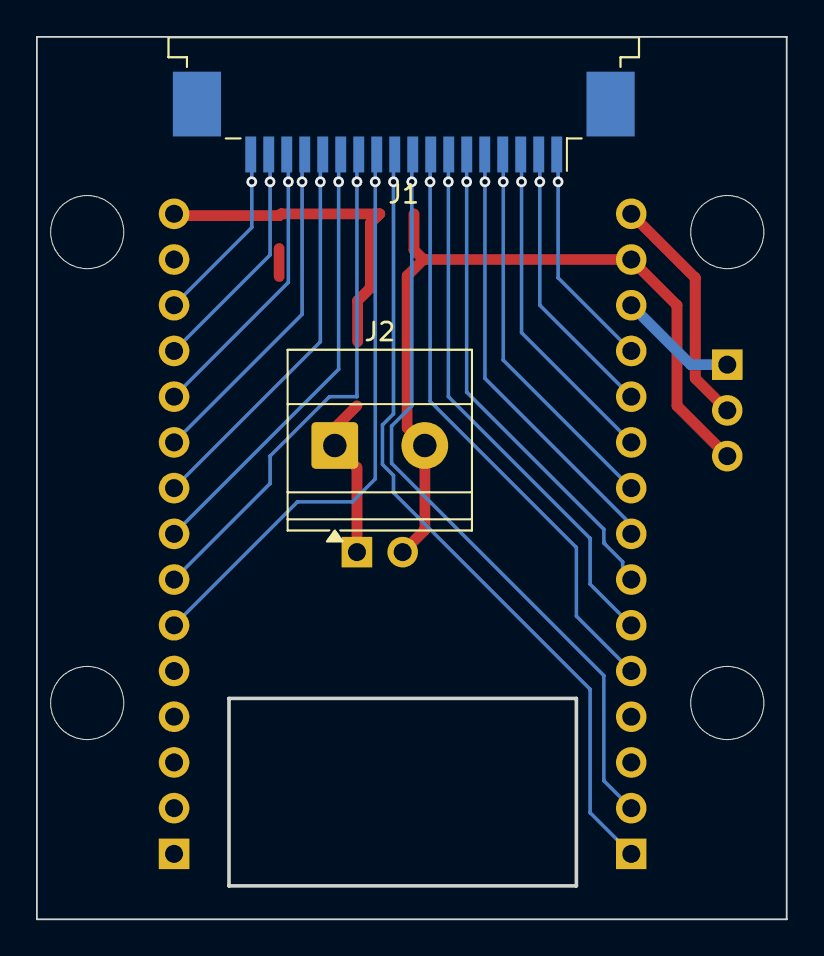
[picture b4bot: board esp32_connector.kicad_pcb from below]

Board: 2 copper layers, 41.7 x 49.0 mm, 9 parts (2 on the bottom side), 24 nets.

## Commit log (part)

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2026-03-01 move servo mainboard folder
2026-05-02 mainboard kicad
2026-05-02 hardware gitignore and fixes
2026-05-03 step 1
2026-05-03 removal of old namespace-name array
2026-05-03 phase 2 refactoring
2026-05-03 component extraction
2026-05-03 more docs - sdkconfig for components
2026-05-03 complete phase 1 arch refactoring
2026-05-03 remove legacy code
2026-05-03 legacy code removal again
2026-05-03 clean base before refactoring components
2026-05-03 extract config manager
2026-05-03 shared types
2026-05-03 update docs
2026-05-03 decouple rpc_commands
2026-05-03 decouple components from main
2026-05-03 fix arch diagram
2026-05-03 extract kinematics, locomotion and config
2026-05-03 extract kinematics, locomotion and config part 2
2026-05-03 extract kpp
2026-05-03 docs update
2026-05-03 more docs
2026-05-03 consolidaste documentation
2026-05-03 refactor config namespaces into separate files
2026-05-03 buddy insturctions
2026-05-03 docs: align namespace naming with short console names
2026-05-03 feat(config): add leg_geom namespace wiring and persistence
2026-05-03 config manager add anmesapce checklist
2026-05-03 update docs leg_geom
2026-05-03 use sotred values for leg_geom
2026-05-03 motion limits config namespace
2026-05-04 docs: sync config and KPP status with current implementation
2026-05-04 Add controller config namespace and runtime wiring
2026-05-04 Implement wifi config namespace and runtime wiring
2026-05-04 plan
2026-05-04 phase 1
2026-05-04 phase 2
2026-05-04 wifi extraction
2026-05-04 extraction of domain
2026-05-04 namespace owned apis
2026-05-04 change defaults and persistance interfacte
2026-05-04 consumer indluce migration
2026-05-04 plan update; remove config_manager.h
2026-05-04 folderization and lessons learnt
2026-05-05 template for config manager
2026-05-12 improve docs
2026-05-12 improve docs 2
2026-05-12 todo updates
2026-05-12 remove duplicated configuration
2026-05-12 namespace servo_map with gpio and driver selection
2026-05-12 config: add gait namespace and wire runtime consumers
2026-05-12 controller: add deadband and failsafe command profile
2026-05-12 cleanup: remove stale KPP constants and robot debug fields
2026-05-12 docs: update config persistence design notes
2026-05-12 wifi: enforce strict namespace-backed init with no fallbacks
2026-05-12 actuation: fail fast when joint calibration is missing or invalid
2026-05-12 first integration tests
2026-05-13 first integration tests and compile fix
2026-05-13 leg geom namespace tests
2026-05-13 tests for motnion lim and servo map namespaces
2026-05-13 gait and joint_cal namespaces tests
2026-05-13 first review of docs
2026-05-14 remove reference to history
2026-05-14 bottom plate design
2026-05-15 refactor instructions into skills
2026-05-15 top and bottom plates
2026-05-17 test for factory reset
2026-05-17 c-hinge
2026-05-24 new models
2026-05-24 standardize naming HEXAPOD, AGNETS file
2026-05-24 models
2026-05-27 fixed corner
2026-05-28 model updastes
2026-06-07 fixed a few thigs with model
2026-06-09 chore: reorganize into firmware monorepo layout
2026-06-09 docs: refresh monorepo readmes and relocate license
2026-06-09 docs: expand project README details
2026-06-09 docs: refine project readme and workspace
2026-06-10 move pin connection in rj11
2026-06-10 Update V2 board schematics and footprints
2026-06-10 Use 1210 footprint for legboard shunts
2026-06-10 settings
2026-06-11 latest leg schema changes
2026-06-11 first iteration of leg board
2026-06-13 manual fixes for mainboard
2026-06-13 allow mainboard cli for copilot
2026-06-13 revised mainbaord schematics
2026-06-15 powerboard changes
2026-06-15 firmware versioning applied
2026-06-20 leg v2
2026-06-20 powerboard layout
2026-06-20 powerboard layout adjustments
2026-06-20 powerboard rc1
2026-06-21 mainboard physical design
2026-06-22 new docs
2026-06-22 readme fix
